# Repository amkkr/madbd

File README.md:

# madbd

最下段のキー数が少ないおおむね格子状のキーボード

## Images

### 0.0.1

### 0.0.2

### 0.0.3

### 1.0.0

## Show Links

- raspberry pi pico datasheet
  - <https://datasheets.raspberrypi.com/pico/pico-datasheet.pdf>
- raspberry pi pico KiCad files
  - <https://datasheets.raspberrypi.com/rp2040/VGA-KiCAD.zip>
- Automated wiring tool
  - <https://github.com/freerouting/freerouting>

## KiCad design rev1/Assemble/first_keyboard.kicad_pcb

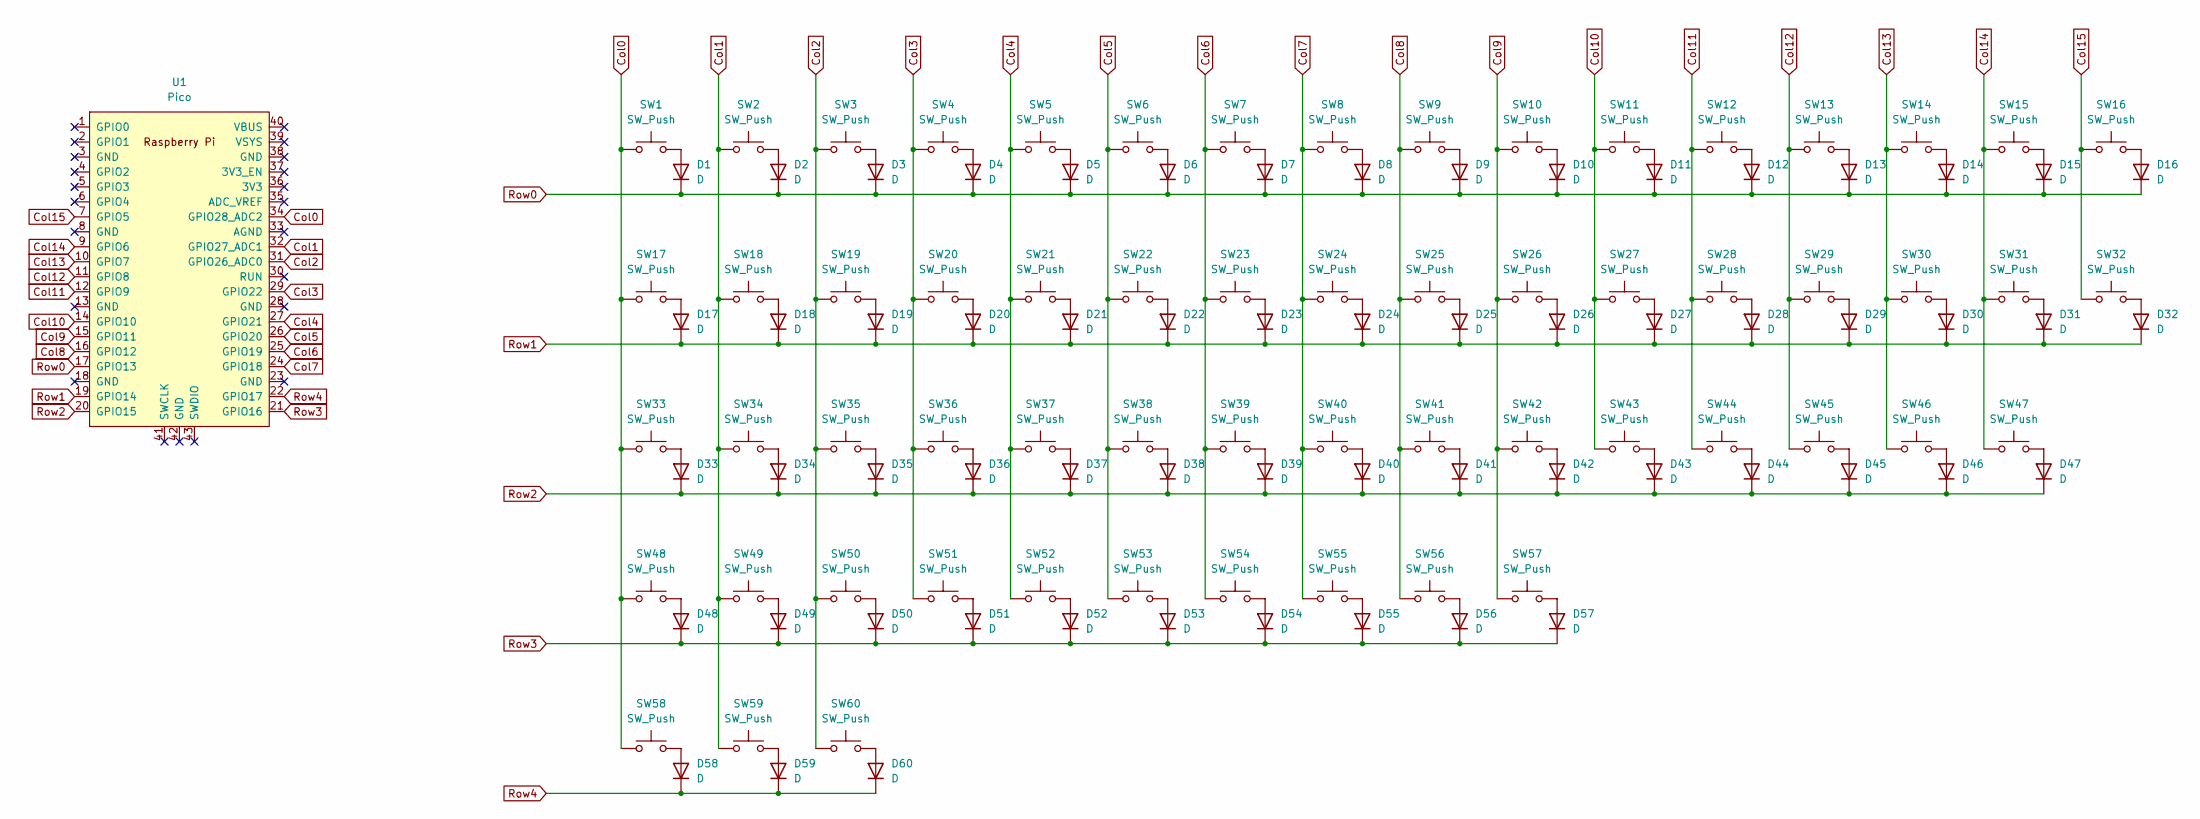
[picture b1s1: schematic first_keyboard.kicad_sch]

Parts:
D1, D2, D3, D4, D5, D6, D7, D8, D9, D10, D11, D12, D13, D14, D15, D16, D17, D18, D19, D20, D21, D22, D23, D24, D25, D26, D27, D28, D29, D30, D31, D32, D33, D34, D35, D36, D37, D38, D39, D40, D41, D42, D43, D44, D45, D46, D47, D48, D49, D50, D51, D52, D53, D54, D55, D56, D57, D58, D59, D60: D; Diode_TH_SMD
SW1, SW2, SW3, SW4, SW5, SW6, SW7, SW8, SW9, SW10, SW11, SW12, SW13, SW14, SW15, SW16, SW17, SW18, SW19, SW20, SW21, SW22, SW23, SW24, SW25, SW26, SW27, SW28, SW29, SW30, SW31, SW33, SW34, SW35, SW36, SW37, SW38, SW39, SW40, SW41, SW42, SW43, SW44, SW45, SW46, SW47, SW48, SW49, SW50, SW51, SW52, SW53, SW54, SW55, SW56, SW57, SW59, SW60: SW_Push; CherryMX_Hotswap_1u
SW32, SW58: SW_Push; CherryMX_Hotswap_2u
U1: Pico; RPi_Pico_SMD_TH

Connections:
Col0: SW1.1, SW17.1, SW33.1, SW48.1, SW58.1, U1.34 (GPIO28_ADC2)
Col1: SW2.1, SW18.1, SW34.1, SW49.1, SW59.1, U1.32 (GPIO27_ADC1)
Col2: SW3.1, SW19.1, SW35.1, SW50.1, SW60.1, U1.31 (GPIO26_ADC0)
Col3: SW4.1, SW20.1, SW36.1, SW51.1, U1.29 (GPIO22)
Col4: SW5.1, SW21.1, SW37.1, SW52.1, U1.27 (GPIO21)
Col5: SW6.1, SW22.1, SW38.1, SW53.1, U1.26 (GPIO20)
Col6: SW7.1, SW23.1, SW39.1, SW54.1, U1.25 (GPIO19)
Col7: SW8.1, SW24.1, SW40.1, SW55.1, U1.24 (GPIO18)
Col8: SW9.1, SW25.1, SW41.1, SW56.1, U1.16 (GPIO12)
Col9: SW10.1, SW26.1, SW42.1, SW57.1, U1.15 (GPIO11)
Col10: SW11.1, SW27.1, SW43.1, U1.14 (GPIO10)
Col11: SW12.1, SW28.1, SW44.1, U1.12 (GPIO9)
Col12: SW13.1, SW29.1, SW45.1, U1.11 (GPIO8)
Col13: SW14.1, SW30.1, SW46.1, U1.10 (GPIO7)
Col14: SW15.1, SW31.1, SW47.1, U1.9 (GPIO6)
Col15: SW16.1, SW32.1, U1.7 (GPIO5)
unnamed: D1.2 (A), SW1.2
unnamed: D2.2 (A), SW2.2
unnamed: D3.2 (A), SW3.2
unnamed: D4.2 (A), SW4.2
unnamed: D5.2 (A), SW5.2
unnamed: D6.2 (A), SW6.2
unnamed: D7.2 (A), SW7.2
unnamed: D8.2 (A), SW8.2
unnamed: D9.2 (A), SW9.2
unnamed: D10.2 (A), SW10.2
unnamed: D11.2 (A), SW11.2
unnamed: D12.2 (A), SW12.2
unnamed: D13.2 (A), SW13.2
unnamed: D14.2 (A), SW14.2
unnamed: D15.2 (A), SW15.2
unnamed: D16.2 (A), SW16.2
unnamed: D17.2 (A), SW17.2
unnamed: D18.2 (A), SW18.2
unnamed: D19.2 (A), SW19.2
unnamed: D20.2 (A), SW20.2
unnamed: D21.2 (A), SW21.2
unnamed: D22.2 (A), SW22.2
unnamed: D23.2 (A), SW23.2
unnamed: D24.2 (A), SW24.2
unnamed: D25.2 (A), SW25.2
unnamed: D26.2 (A), SW26.2
unnamed: D27.2 (A), SW27.2
unnamed: D28.2 (A), SW28.2
unnamed: D29.2 (A), SW29.2
unnamed: D30.2 (A), SW30.2
unnamed: D31.2 (A), SW31.2
unnamed: D32.2 (A), SW32.2
unnamed: D33.2 (A), SW33.2
unnamed: D34.2 (A), SW34.2
unnamed: D35.2 (A), SW35.2
unnamed: D36.2 (A), SW36.2
unnamed: D37.2 (A), SW37.2
unnamed: D38.2 (A), SW38.2
unnamed: D39.2 (A), SW39.2
unnamed: D40.2 (A), SW40.2
unnamed: D41.2 (A), SW41.2
unnamed: D42.2 (A), SW42.2
unnamed: D43.2 (A), SW43.2
unnamed: D44.2 (A), SW44.2
unnamed: D45.2 (A), SW45.2
unnamed: D46.2 (A), SW46.2
unnamed: D47.2 (A), SW47.2
unnamed: D48.2 (A), SW48.2
unnamed: D49.2 (A), SW49.2
unnamed: D50.2 (A), SW50.2
unnamed: D51.2 (A), SW51.2
unnamed: D52.2 (A), SW52.2
unnamed: D53.2 (A), SW53.2
unnamed: D54.2 (A), SW54.2
unnamed: D55.2 (A), SW55.2
unnamed: D56.2 (A), SW56.2
unnamed: D57.2 (A), SW57.2
unnamed: D58.2 (A), SW58.2
unnamed: D59.2 (A), SW59.2
unnamed: D60.2 (A), SW60.2
Row0: D1.1 (K), D2.1 (K), D3.1 (K), D4.1 (K), D5.1 (K), D6.1 (K), D7.1 (K), D8.1 (K), D9.1 (K), D10.1 (K), D11.1 (K), D12.1 (K), D13.1 (K), D14.1 (K), D15.1 (K), D16.1 (K), U1.17 (GPIO13)
Row1: D17.1 (K), D18.1 (K), D19.1 (K), D20.1 (K), D21.1 (K), D22.1 (K), D23.1 (K), D24.1 (K), D25.1 (K), D26.1 (K), D27.1 (K), D28.1 (K), D29.1 (K), D30.1 (K), D31.1 (K), D32.1 (K), U1.19 (GPIO14)
Row2: D33.1 (K), D34.1 (K), D35.1 (K), D36.1 (K), D37.1 (K), D38.1 (K), D39.1 (K), D40.1 (K), D41.1 (K), D42.1 (K), D43.1 (K), D44.1 (K), D45.1 (K), D46.1 (K), D47.1 (K), U1.20 (GPIO15)
Row3: D48.1 (K), D49.1 (K), D50.1 (K), D51.1 (K), D52.1 (K), D53.1 (K), D54.1 (K), D55.1 (K), D56.1 (K), D57.1 (K), U1.21 (GPIO16)
Row4: D58.1 (K), D59.1 (K), D60.1 (K), U1.22 (GPIO17)

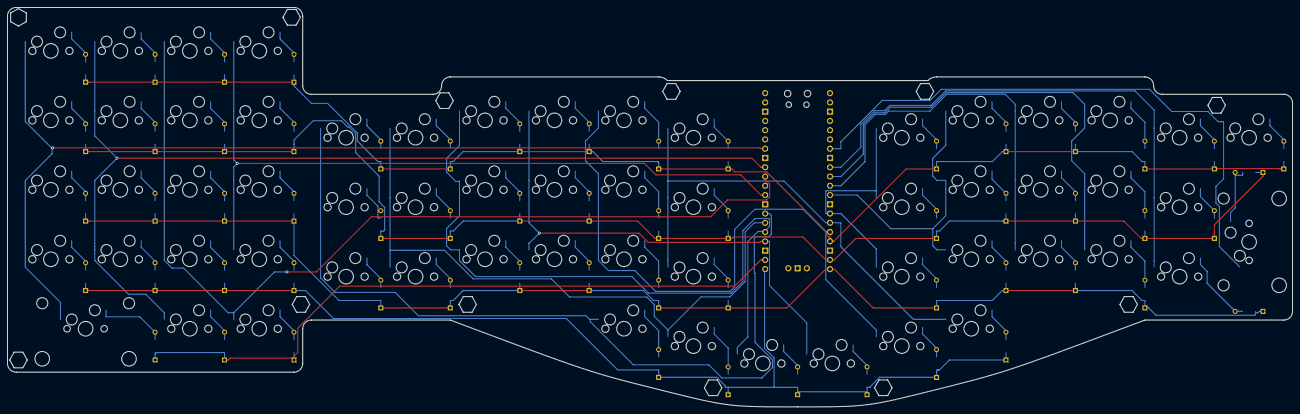
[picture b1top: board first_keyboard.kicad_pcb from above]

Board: 2 copper layers, 352.4 x 109.5 mm, 133 parts (1 on the bottom side), 81 nets.

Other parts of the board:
ref1, ref2, ref3, ref4, ref5, ref6, ref7, ref8, ref9, ref11, ref12, ref13: val; m2_Spacer_Hole_hex

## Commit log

2024-03-01 feat: key switches wiring
2024-03-01 add gitignore
2024-03-01 add LICENSE
2024-03-01 add README
2024-03-01 fix typo
2024-03-01 fix ignore
2024-03-03 feat: change rasp pico
2024-03-03 add: layout.json
2024-03-04 add: links in README
2024-03-08 feat: picoに配線した
2024-03-08 feat: PWR_FLAG違反修正
2024-03-09 feat: ナンバリング修正
2024-03-09 fix: gitignore
2024-03-21 feat: pcbのスイッチ整列\
2024-03-21 feat:ダイオードの番号降り直しと整列\
2024-03-21 feat: すべて整列済み\
2024-03-21 feat: ダイオードそろえた
2024-03-21 add: Top plate
2024-03-21 feat: m3spacer
2024-03-21 feat: picoを裏面に
2024-03-21 add: Bottom
2024-03-21 feat: ダイオードをスイッチの近くに大移動
2024-03-21 feat: 配線
2024-03-23 add: PCB drill files
2024-03-23 add: Top-plate drill files
2024-03-23 add: Bottom-plate drill files
2024-03-23 add: zips
2024-04-06 fix: ボードの反転を意識してタグを振りなおした
2024-04-06 fix: ねじ穴に変更
2024-04-06 feat: 回路図にスイッチを追加
2024-04-06 feat: 新デザインと配線
2024-04-06 feat: 外形追加、pdf更新
2024-04-07 feat: 外形更新、スルーホール追加、配線追加
2024-04-07 add: top_plate
2024-04-07 delete: Bottom
2024-04-07 feat: 刻印追加
2024-04-07 add: gerber出力
2024-04-07 add: zip
2024-04-07 chore: checked gerber view
2024-04-21 add: images
2024-04-21 chore: update readme
2024-05-11 add: 0.0.2 image
2024-05-11 タグ付与のため
2024-05-12 feat: 回路図をpicoがスイッチと同じ面に来る想定のものに変更
2024-05-12 feat: PCBの配置を変更
2024-05-12 fix: 左右とpicoの整列
2024-05-12 feat: 角度8, 左右幅初期位置
2024-05-12 delete: test.pdf
2024-05-12 feat: lotate 12, width 4
2024-06-30 update: kicad version
2024-06-30 feat: lotate 10 両端のキーは無回転
2024-08-03 feat: 小指カラムをさげる part1
2024-08-03 feat: 小指カラムをさげる part2
2024-08-03 fix: ignore DS_Store
2024-08-03 fix: 配線を修正
2024-08-03 feat: dsnファイルを最新に
2024-08-03 feat: 縦配線を追加
2024-08-03 feat: Col0の配線と左手カソードの配線
2024-08-03 feat: →手カソードの配線
2024-08-03 feat: col0の配線修正
2024-08-03 feat: 左側配線終了
2024-08-03 feat: 90度排除
2024-08-04 feat: ガーバーファイル出力
2024-08-04 fix: ファイル閉じた際の更新
2024-08-05 chore: update kicad version
2024-09-07 remove: ignored mesh
2024-09-07 fix: remove sch ERC error
2024-09-07 feat: 外形線まで
2024-09-07 feat: 外形線修正
2024-09-07 feat: ダイオード位置変更
2024-09-08 feat: 輪郭線変更
2024-09-08 feat: スペース繋げて外形変更
2024-09-08 feat: Topからダイオード削除
2024-09-08 feat: Topネジ穴追加
2024-09-08 feat: ダイオード実装面変更
2024-09-08 feat: ６角スペーサー穴追加
2024-09-08 feat: pcbのネジ穴にRevを振る
2024-09-08 feat: TOPに模様追加
2024-09-08 feat: ドリルファイル生成
2024-09-08 update: TOP.zip
2024-09-22 fix: ダイオード位置を変更
2024-09-22 update: drill file
2024-09-22 update: plot-file
2024-09-22 delete: PCB gerber
2024-09-22 update: 配線とドリルファイルの更新
2025-02-26 add: madbd4の画像追加
2025-02-26 update: README
2025-11-20 update: kicadバージョン
2025-11-29 feat: スイッチとダイオードは置いた
2025-11-30 feat: 回路図引いた
2025-11-30 feat: ラベル付け直しとフットプリント指定
2025-11-30 feat: PCB部品配置
2025-11-30 feat: アウトライン作成
2025-12-01 feat: dir整理,
2025-12-01 feat: スペーサー穴追加
2025-12-01 add: Topプレート追加
2025-12-01 feat: ネジ穴位置調整
2025-12-01 add: fox
2025-12-01 add: gerber
2025-12-01 remove: old gerber
2025-12-20 update: madbd5 column
